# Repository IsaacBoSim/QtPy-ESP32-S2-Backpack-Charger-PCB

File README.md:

# QtPy-ESP32-S2-Backpack-Charger-PCB

This is a PCB design for a backpack charger for the ESP32-S2. It is designed to be used with the [Adafruit ESP32-S2 Feather](https://www.adafruit.com/product/4870) and the [Adafruit FeatherWing OLED](https://www.adafruit.com/product/4650).

The PCB is based off of the lion battery charger backpack for the ESP32 Feather by [Adafruit](https://learn.adafruit.com/adafruit-feather-s2-esp32-s2/overview).

The backpack charger is designed to be used with a 3.7V 350mAh LiPo battery. The battery can be charged using a USB-C cable. The backpack charger has a USB-C port for charging the battery and a JST PH 2-pin connector for connecting the battery to the ESP32-S2.

Listed below are the components used in the backpack charger:
- MCP73831T-2ACI/OT	SOT23-5
- EG1390 Switch	EG1390
- USB-C Connector	USB-C-31-M-12
- Diode	SOD-123FL
- PZT3904 Transistor	SOT223
- LED	LED-1206 1x
- 2.2kΩhm Resistor	1206
- 2x 100kΩhm Resistor	1206
- 2x 5.1kΩhm Resistor	1206
- 100Ωhm Resistor	1206
- 2x 10 μF Capacitor	1206 6.3V-20%

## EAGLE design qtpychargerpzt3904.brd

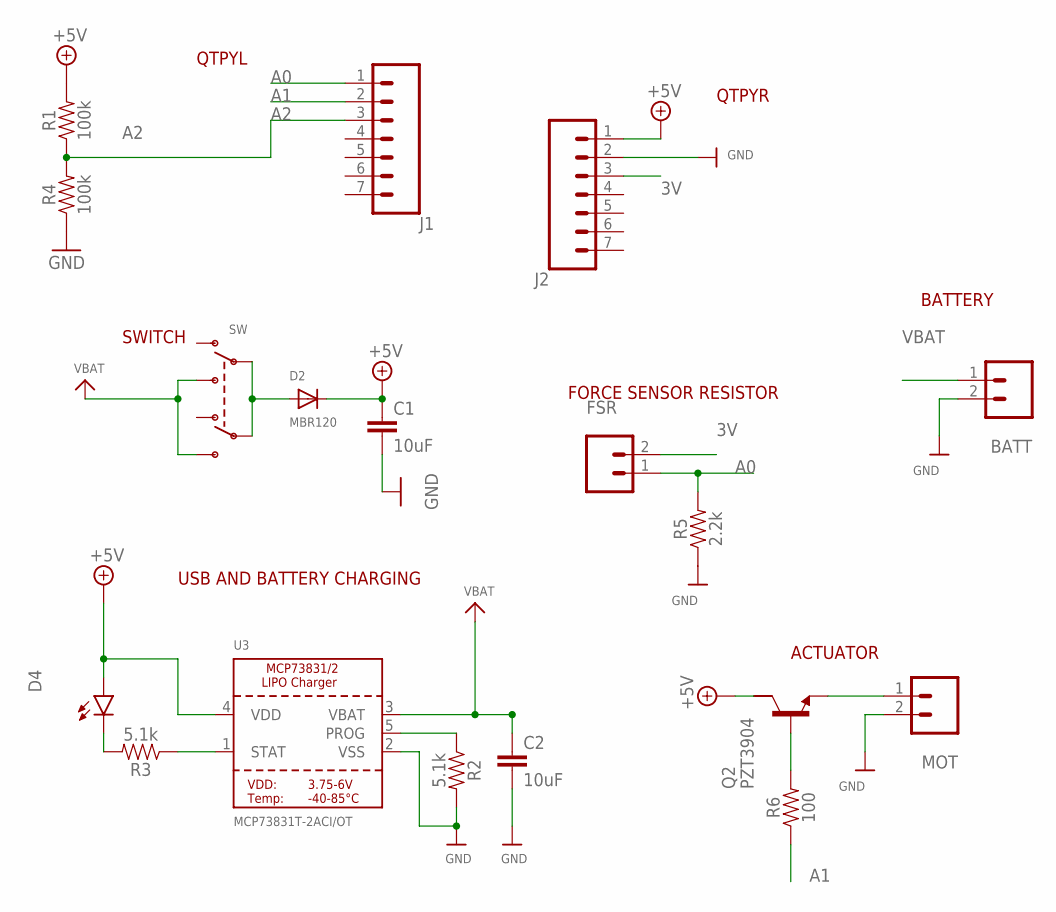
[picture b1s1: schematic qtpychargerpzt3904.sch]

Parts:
BATT: CONN_02; 1X02
C1, C2: 10uF; 1206
D2: MBR120; SOD-123FL
D4: LED1206; LED-1206
FSR: CONN_02; 1X02
J1, J2: CONN_07; 1X07
MOT: CONN_02; 1X02
Q2: PZT3904; SOT223
R1, R4: 100k; 1206
R2, R3: 5.1k; 1206
R5: 2.2k; 1206
R6: 100; 1206
SW: SWITCH_DPDTEG1390; EG1390
U3: MCP73831T-2ACI/OT; SOT23-5

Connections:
3V: FSR.2, J2.3
+5V: C1.1, D2.C, D4.A, J2.1, Q2.2 (C), R1.2, U3.4 (VDD)
A0: FSR.1, J1.1, R5.2
A1: J1.2, R6.1
A2: J1.3, R1.1, R4.2
GND: BATT.2, C1.2, C2.2, J2.2, MOT.2, R2.2, R4.1, R5.1, U3.2 (VSS)
unnamed: Q2.1 (B), R6.2
unnamed: D4.C, R3.2
unnamed: R3.1, U3.1 (STAT)
unnamed: R2.1, U3.5 (PROG)
unnamed: MOT.1, Q2.3 (E)
unnamed: D2.A, SW.P1, SW.P2
VBAT: BATT.1, C2.1, SW.S1, SW.S2, U3.3 (VBAT)

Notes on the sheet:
USB AND BATTERY CHARGING
ACTUATOR
FORCE SENSOR RESISTOR
BATTERY
SWITCH
QTPYL
QTPYR

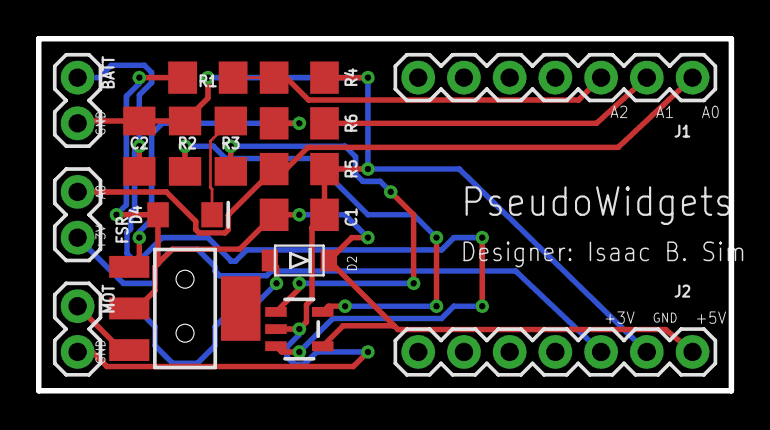
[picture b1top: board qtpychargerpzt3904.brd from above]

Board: 2 copper layers, 38.5 x 19.6 mm, 18 parts (1 on the bottom side), 13 nets.

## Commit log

2024-04-19 added files for version control

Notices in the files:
parts and their libraries:
microbuilder: This work is placed in the public domain, and may be freely used for commercial and non-commercial work with the following conditions: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
SparkFun-Connectors: Licensing: Creative Commons ShareAlike 4.0 International - https://creativecommons.org/licenses/by-sa/4.0
